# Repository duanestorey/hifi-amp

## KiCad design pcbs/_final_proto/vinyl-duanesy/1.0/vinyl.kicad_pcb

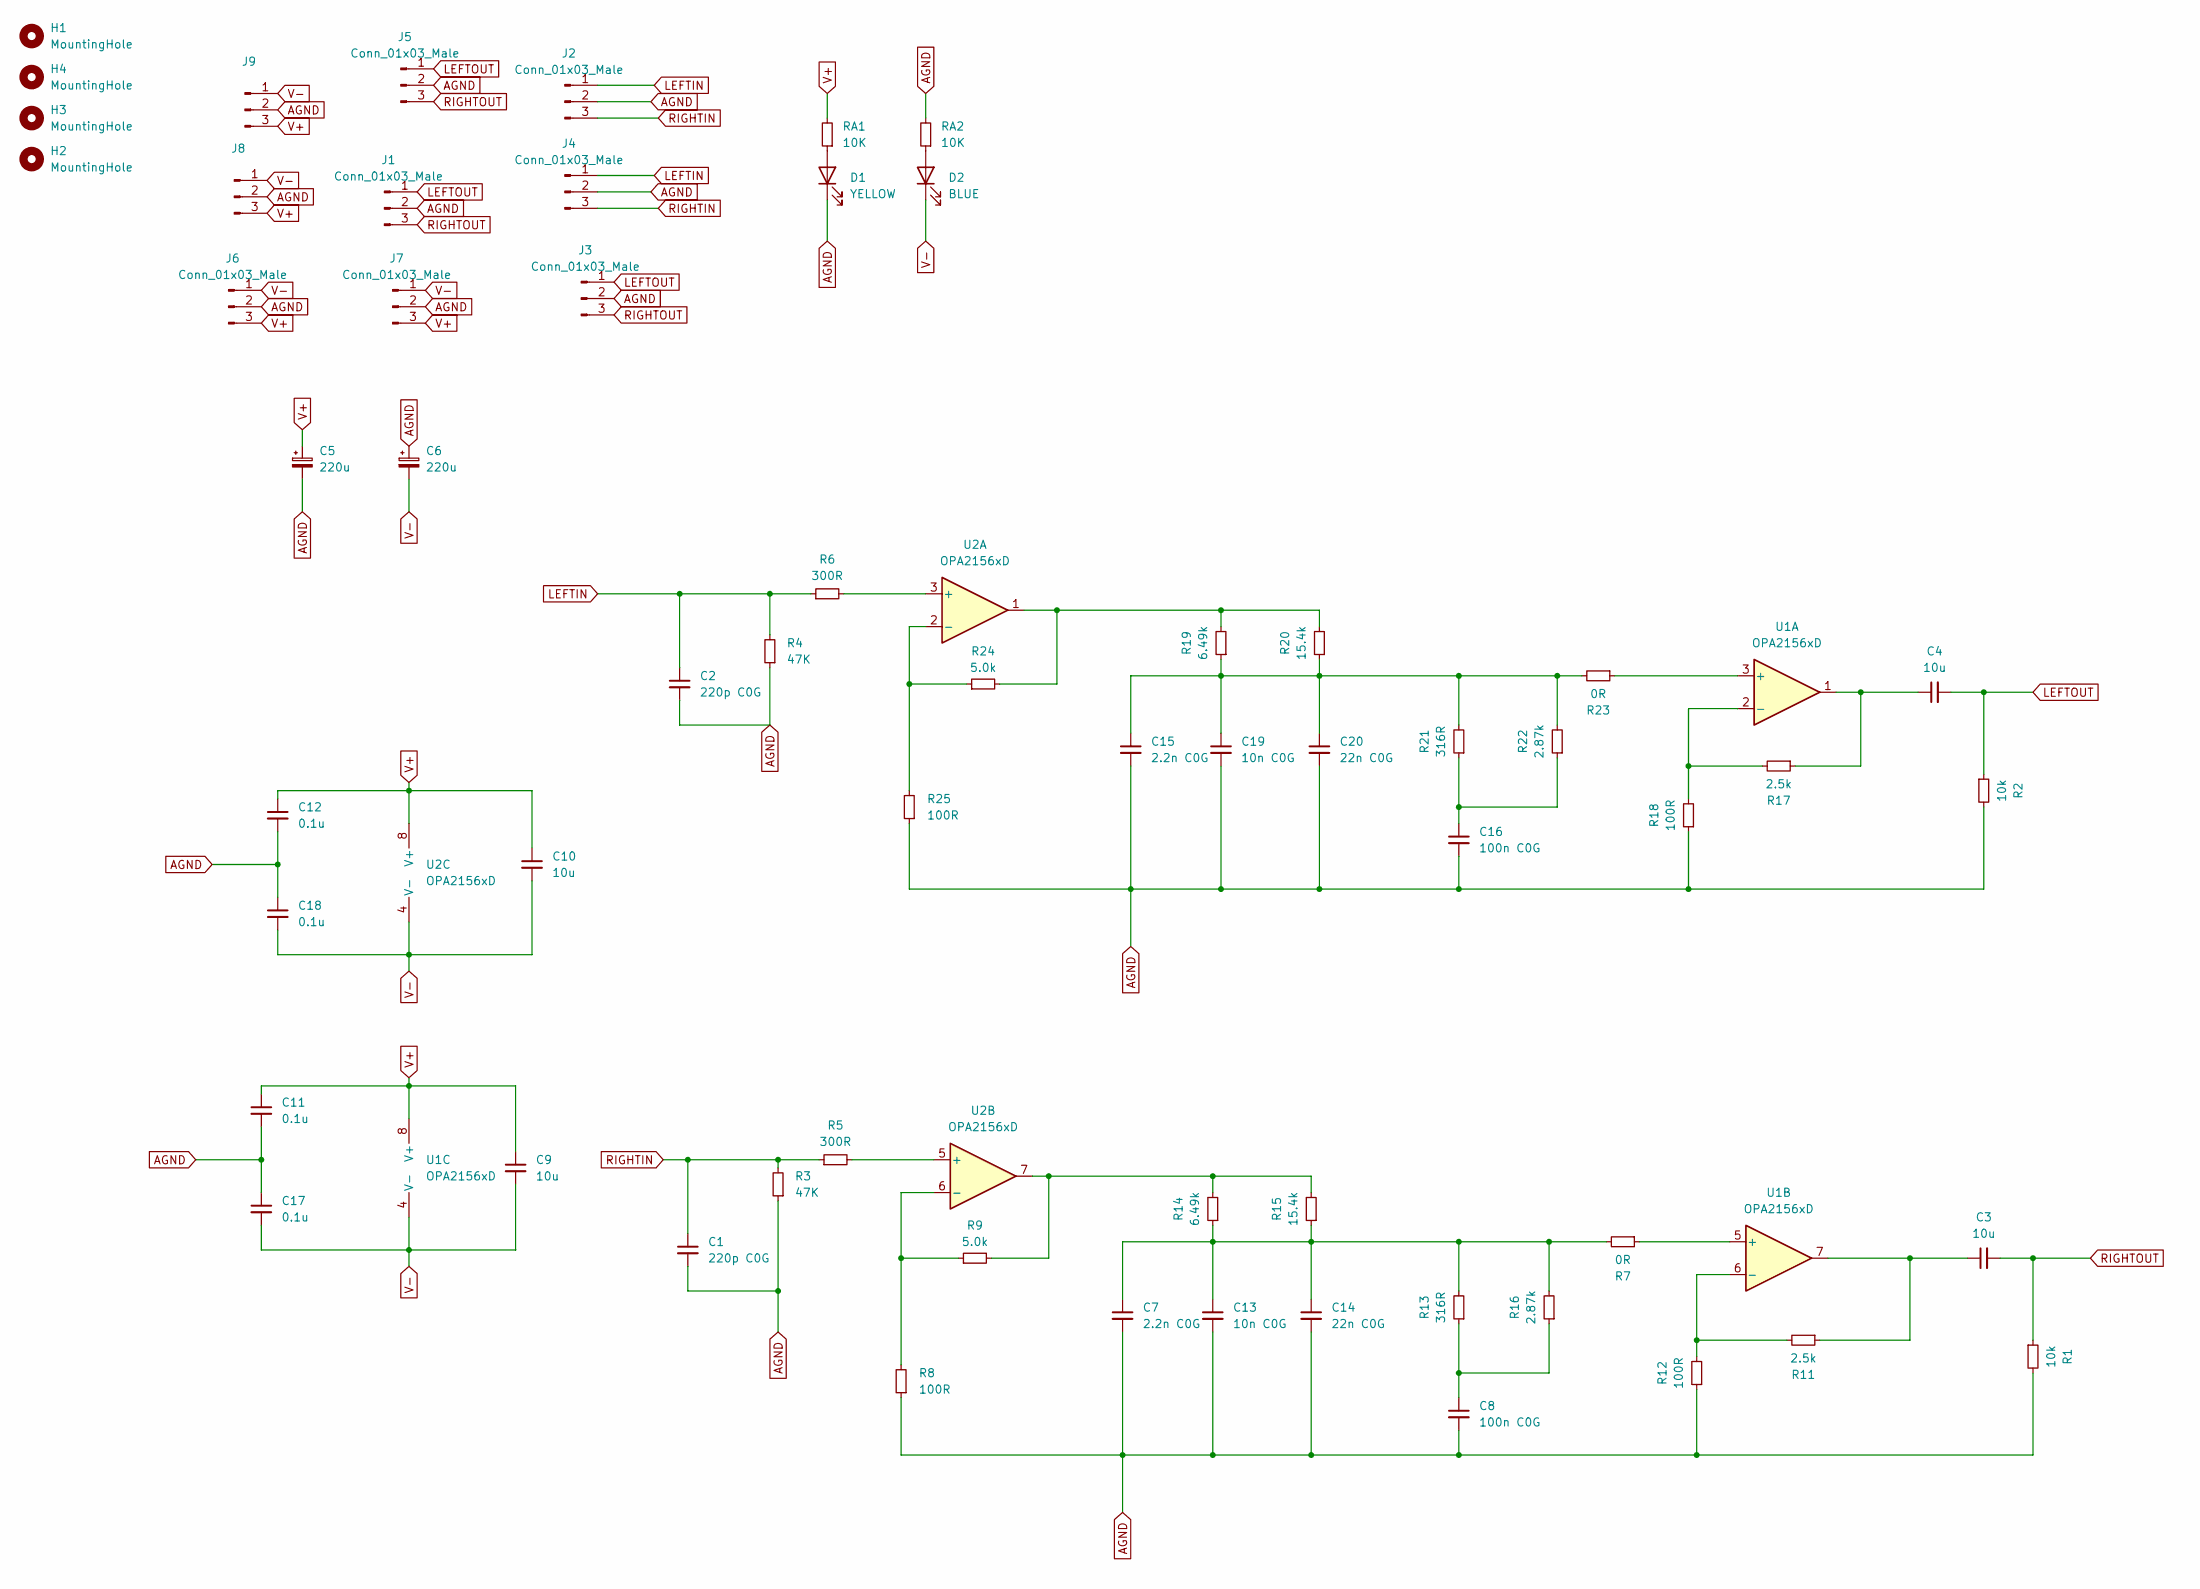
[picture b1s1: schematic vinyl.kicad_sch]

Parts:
C1, C2: 220p C0G; C_0805_2012Metric_Pad1.18x1.45mm_HandSolder_Duane; Mouser 791-0805N221F500CT
C3, C4: 10u; CP_Radial_D5.0mm_P2.00mm
C5, C6: 220u; CP_Elec_6.3x7.7
C7, C15: 2.2n C0G; C_0805_2012Metric_Pad1.18x1.45mm_HandSolder_Duane; Mouser 791-0805N222F500CT
C8, C16: 100n C0G; C_1206_3216Metric_Pad1.33x1.80mm_HandSolder_Duane; Mouser 81-GRT31C5C1H104FA2L
C9, C10: 10u; C_1206_3216Metric_Pad1.33x1.80mm_HandSolder_Duane
C11, C12, C17, C18: 0.1u; C_0805_2012Metric_Pad1.18x1.45mm_HandSolder_Duane
C13, C19: 10n C0G; C_0805_2012Metric_Pad1.18x1.45mm_HandSolder_Duane; Mouser 791-0805N103F500CT
C14, C20: 22n C0G; C_0805_2012Metric_Pad1.18x1.45mm_HandSolder_Duane; Mouser 81-GCM21B5C1H223FA6L
D1: YELLOW; LED_0805_2012Metric_Pad_HandSolder_Duane
D2: BLUE; LED_0805_2012Metric_Pad_HandSolder_Duane
H1, H2, H3, H4: MountingHole; MountingHole_3.2mm_M3_DIN965_Pad_TopOnly
J1, J2, J8, J9: Conn_01x03_Male; JST_PH_B3B-PH-K_1x03_P2.00mm_Vertical
J3, J4, J6, J7: Conn_01x03_Male; TerminalBlock_Phoenix_PT-1,5-3-5.0-H_1x03_P5.00mm_Horizontal
J5: Conn_01x03_Male; PinHeader_1x03_P2.54mm_Vertical
R1, R2: 10k; R_0805_2012Metric_Pad1.20x1.40mm_HandSolder_Duane; Mouser 754-RG2012P-103-B-T5
R3, R4: 47K; R_0805_2012Metric_Pad1.20x1.40mm_HandSolder_Duane; Mouser 603-RT0805BRD0747KL
R5, R6: 300R; R_0805_2012Metric_Pad1.20x1.40mm_HandSolder_Duane; Mouser 603-RT0805BRD07300RL
R7, R23: 0R; R_0805_2012Metric_Pad1.20x1.40mm_HandSolder_Duane; Mouser 594-MCU0805MZ0000ZP5
R8, R12, R18, R25: 100R; R_0805_2012Metric_Pad1.20x1.40mm_HandSolder_Duane; Mouser 708-RNCF0805BTE100R
R9, R24: 5.0k; R_0805_2012Metric_Pad1.20x1.40mm_HandSolder_Duane; Mouser 652-CRT0805BY5001EAS
R11, R17: 2.5k; R_0805_2012Metric_Pad1.20x1.40mm_HandSolder_Duane; Mouser PTN0805E2501BST1
R13, R21: 316R; R_0805_2012Metric_Pad1.20x1.40mm_HandSolder_Duane; Mouser 71-TNPW0805316RBEEA
R14, R19: 6.49k; R_0805_2012Metric_Pad1.20x1.40mm_HandSolder_Duane; Mouser RT0805BRD076K49L
R15, R20: 15.4k; R_0805_2012Metric_Pad1.20x1.40mm_HandSolder_Duane; Mouser RNCS0805BTE15K4
R16, R22: 2.87k; R_0805_2012Metric_Pad1.20x1.40mm_HandSolder_Duane; Mouser 667-ERA-6AEB2871V
RA1, RA2: 10K; R_0805_2012Metric_Pad1.20x1.40mm_HandSolder_Duane
U1, U2: OPA2156xD; DIP-8_W7.62mm_Socket

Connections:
AGND: C1.2, C2.2, C5.2, C6.1, C7.2, C8.2, C11.2, C12.2, C13.2, C14.2, C15.2, C16.2, C17.1, C18.1, C19.2, C20.2, D1.1 (K), J1.2, J2.2, J3.2, J4.2, J5.2, J6.2, J7.2, J8.2, J9.2, R1.2, R2.2, R3.1, R4.1, R8.1, R12.1, R18.1, R25.1, RA2.2
LEFTIN: C2.1, J2.1, J4.1, R4.2, R6.1
LEFTOUT: C4.2, J1.1, J3.1, J5.1, R2.1
unnamed: C3.1, R11.1, U1.7
unnamed: C4.1, R17.1, U1.1
unnamed: C8.1, R13.1, R16.1
unnamed: C7.1, C13.1, C14.1, R7.2, R13.2, R14.1, R15.1, R16.2
unnamed: C15.1, C19.1, C20.1, R19.1, R20.1, R21.2, R22.2, R23.2
unnamed: C16.1, R21.1, R22.1
unnamed: D1.2 (A), RA1.1
unnamed: D2.2 (A), RA2.1
unnamed: R9.2, R14.2, R15.2, U2.7
unnamed: R19.2, R20.2, R24.2, U2.1
unnamed: R23.1, U1.3 (+)
unnamed: R17.2, R18.2, U1.2 (-)
unnamed: R7.1, U1.5 (+)
unnamed: R11.2, R12.2, U1.6 (-)
unnamed: R6.2, U2.3 (+)
unnamed: R24.1, R25.2, U2.2 (-)
unnamed: R5.2, U2.5 (+)
unnamed: R8.2, R9.1, U2.6 (-)
RIGHTIN: C1.1, J2.3, J4.3, R3.2, R5.1
RIGHTOUT: C3.2, J1.3, J3.3, J5.3, R1.1
V+: C5.1, C9.1, C10.1, C11.1, C12.1, J6.3, J7.3, J8.3, J9.3, RA1.2, U1.8 (V+), U2.8 (V+)
V-: C6.2, C9.2, C10.2, C17.2, C18.2, D2.1 (K), J6.1, J7.1, J8.1, J9.1, U1.4 (V-), U2.4 (V-)

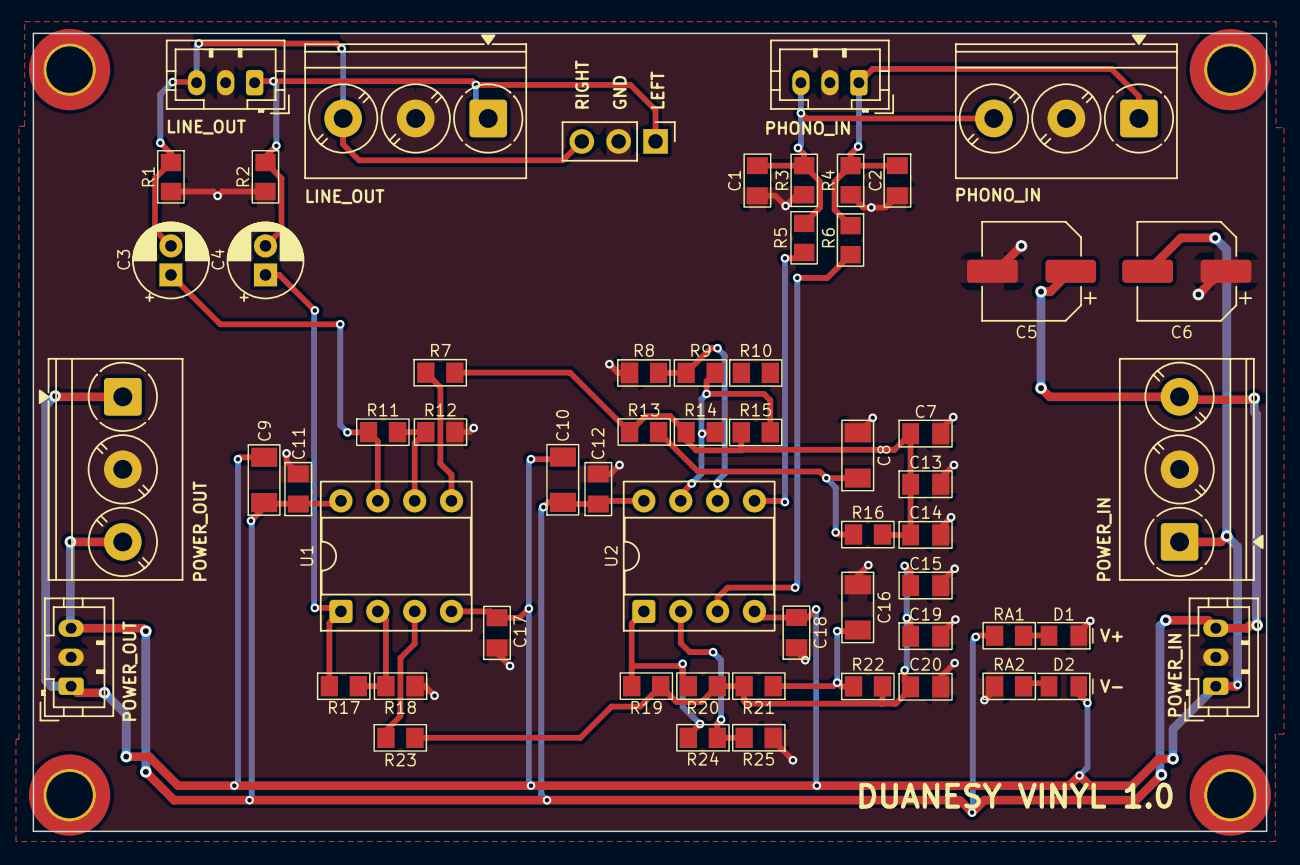
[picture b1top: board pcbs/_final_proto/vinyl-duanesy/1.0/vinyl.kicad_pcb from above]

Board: 2 copper layers, 85.0 x 55.0 mm, 64 parts (0 on the bottom side), 25 nets.

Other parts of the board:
R10: Unconnected; R_0805_2012Metric_Pad1.20x1.40mm_HandSolder_Duane

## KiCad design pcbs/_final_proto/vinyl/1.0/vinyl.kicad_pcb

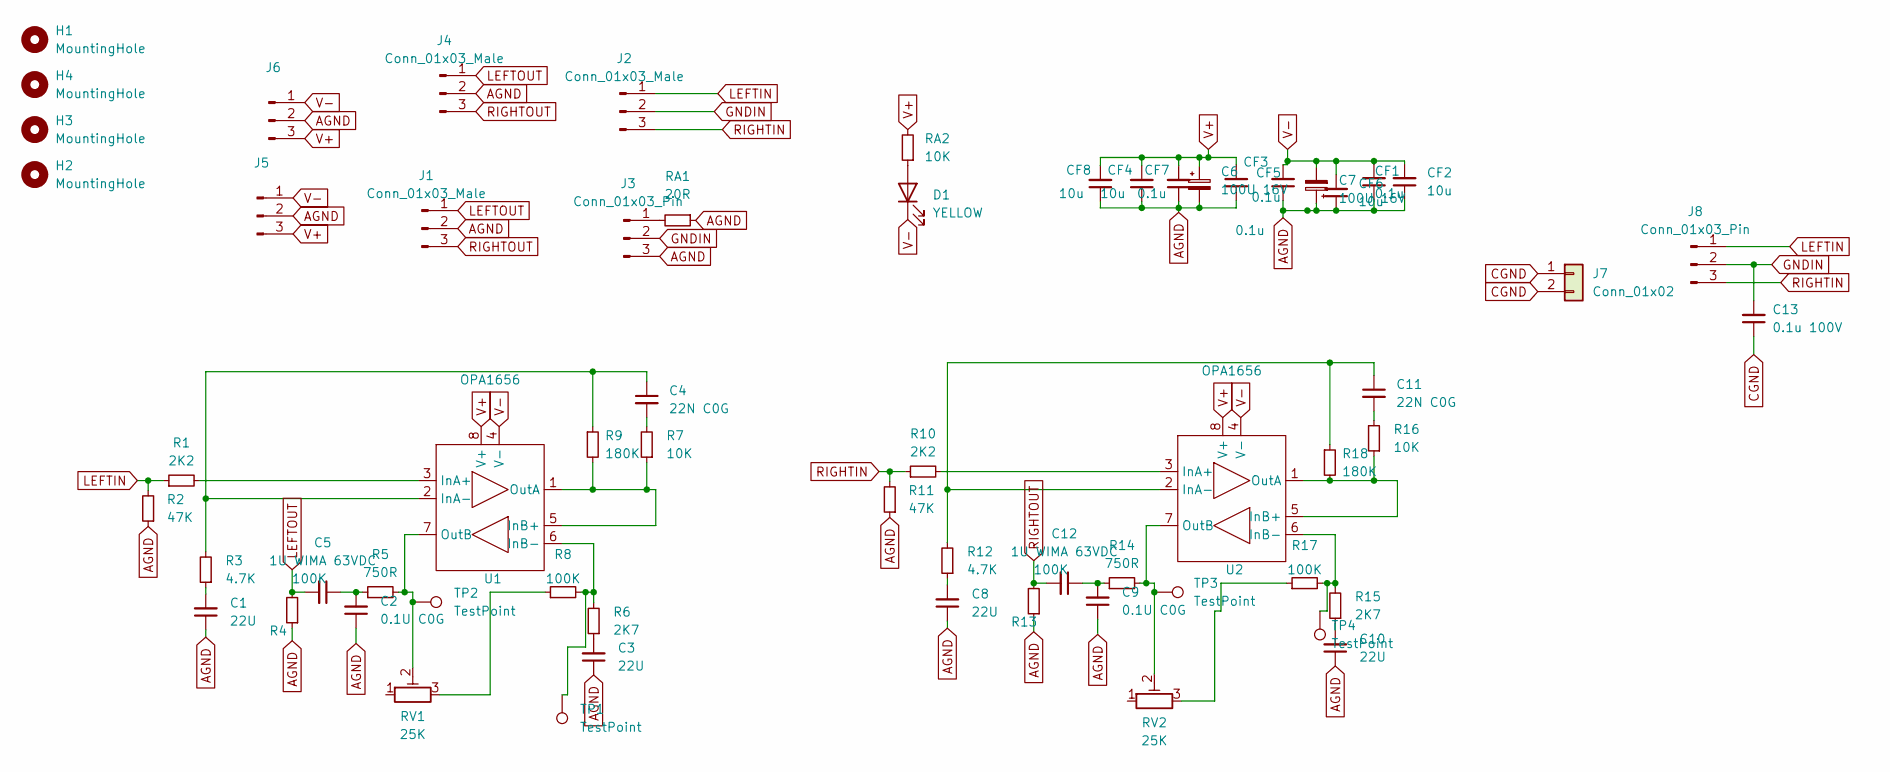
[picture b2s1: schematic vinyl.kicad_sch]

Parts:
C1, C3, C8, C10: 22U; CP_Radial_D6.3mm_P2.50mm
C2, C9: 0.1U C0G; C_1206_3216Metric_Pad1.33x1.80mm_HandSolder; Mouser 81-GRM3195C1H104GA5D
C4, C11: 22N C0G; C_0805_2012Metric_Pad1.18x1.45mm_HandSolder
C5, C12: 1U WIMA 63VDC; C_Rect_L7.2mm_W11.0mm_P5.00mm_FKS2_FKP2_MKS2_MKP2; Mouser 505-MKP2C0411NMN
C6, C7: 100U 16V; CP_Radial_D6.3mm_P2.50mm
C13: 0.1u 100V; C_1206_3216Metric; Mouser 791-1206B104K101CT
CF1, CF3, CF5, CF7: 0.1u; C_0805_2012Metric_Pad1.18x1.45mm_HandSolder
CF2, CF4, CF6, CF8: 10u; C_1206_3216Metric_Pad1.33x1.80mm_HandSolder
D1: YELLOW; LED_0805_2012Metric_Pad1.15x1.40mm_HandSolder
H1, H2, H3, H4: MountingHole; MountingHole_3.2mm_M3_DIN965_Pad_TopOnly
J1, J2, J5, J6: Conn_01x03_Male; JST_PH_B3B-PH-K_1x03_P2.00mm_Vertical
J3: Conn_01x03_Pin; PinHeader_1x03_P2.54mm_Vertical
J4: Conn_01x03_Male; PinHeader_1x03_P2.54mm_Vertical
J7: Conn_01x02; TerminalBlock_Phoenix_PT-1,5-2-3.5-H_1x02_P3.50mm_Horizontal
J8: Conn_01x03_Pin; TerminalBlock_Phoenix_PT-1,5-3-3.5-H_1x03_P3.50mm_Horizontal
R1, R10: 2K2; R_0805_2012Metric_Pad1.20x1.40mm_HandSolder; Mouser 603-RT0805FRE072K2L
R2, R11: 47K; R_0805_2012Metric_Pad1.20x1.40mm_HandSolder; Mouser 603-RT0805FRE0747KL
R3, R12: 4.7K; R_0805_2012Metric_Pad1.20x1.40mm_HandSolder; Mouser 603-RT0805FRE074K7L
R4, R8, R13, R17: 100K; R_0805_2012Metric_Pad1.20x1.40mm_HandSolder; Mouser 603-RT0805FRE10100KL
R5, R14: 750R; R_0805_2012Metric_Pad1.20x1.40mm_HandSolder; Mouser 603-RT0805FRE07750RL
R6, R15: 2K7; R_0805_2012Metric_Pad1.20x1.40mm_HandSolder; Mouser 603-RT0805FRE072K7L
R7, R16: 10K; R_0805_2012Metric_Pad1.20x1.40mm_HandSolder; Mouser 603-RT0805FRE1310KL
R9, R18: 180K; R_0805_2012Metric_Pad1.20x1.40mm_HandSolder; Mouser 603-RT0805FRE07180KL
RA1: 20R; R_0805_2012Metric_Pad1.20x1.40mm_HandSolder
RA2: 10K; R_0805_2012Metric_Pad1.20x1.40mm_HandSolder
RV1, RV2: 25K; Potentiometer_Bourns_3296W_Vertical
TP1, TP2, TP3, TP4: TestPoint; TestPoint_THTPad_1.5x1.5mm_Drill0.7mm
U1, U2: OPA1656; DIP-8_W7.62mm_Socket; Mouser 595-OPA1656IDR

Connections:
AGND: C1.1, C2.1, C3.1, C6.2, C7.1, C8.1, C9.1, C10.1, CF1.1, CF2.1, CF3.1, CF4.1, CF5.1, CF6.1, CF7.1, CF8.1, J1.2, J3.3, J4.2, J5.2, J6.2, R2.1, R4.1, R11.1, R13.1, RA1.1
CGND: C13.1, J7.1, J7.2
GNDIN: C13.2, J2.2, J3.2, J8.2
LEFTIN: J2.1, J8.1, R1.1, R2.2
LEFTOUT: C5.2, J1.1, J4.1, R4.2
unnamed: C1.2, R3.1
unnamed: C2.2, C5.1, R5.1
unnamed: C3.2, R6.1
unnamed: C4.2, R7.2
unnamed: C8.2, R12.1
unnamed: C10.2, R15.1
unnamed: C11.2, R16.2
unnamed: C9.2, C12.1, R14.1
unnamed: D1.2 (A), RA2.1
unnamed: J3.1, RA1.2
unnamed: R8.1, RV1.3
unnamed: R17.1, RV2.3
unnamed: R1.2, U1.3 (InA+)
unnamed: C4.1, R3.2, R9.1, U1.2 (InA-)
unnamed: R7.1, R9.2, U1.1 (OutA), U1.5 (InB+)
unnamed: R6.2, R8.2, TP1.1, U1.6 (InB-)
unnamed: R5.2, RV1.2, TP2.1, U1.7 (OutB)
unnamed: R10.2, U2.3 (InA+)
unnamed: C11.1, R12.2, R18.1, U2.2 (InA-)
unnamed: R16.1, R18.2, U2.1 (OutA), U2.5 (InB+)
unnamed: R15.2, R17.2, TP4.1, U2.6 (InB-)
unnamed: R14.2, RV2.2, TP3.1, U2.7 (OutB)
RIGHTIN: J2.3, J8.3, R10.1, R11.2
RIGHTOUT: C12.2, J1.3, J4.3, R13.2
V+: C6.1, CF3.2, CF4.2, CF7.2, CF8.2, J5.3, J6.3, RA2.2, U1.8 (V+), U2.8 (V+)
V-: C7.2, CF1.2, CF2.2, CF5.2, CF6.2, D1.1 (K), J5.1, J6.1, U1.4 (V-), U2.4 (V-)

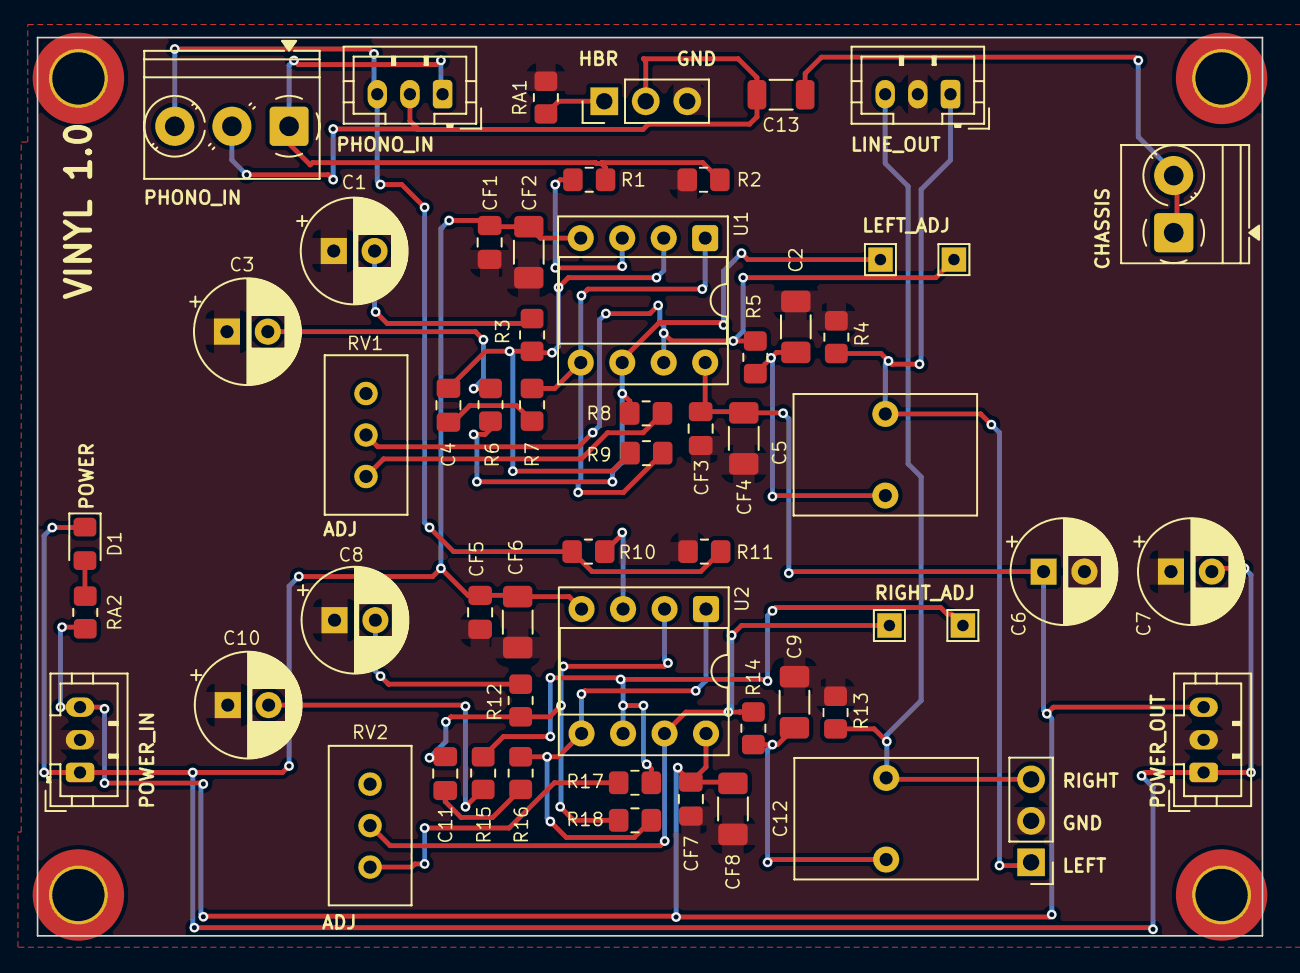
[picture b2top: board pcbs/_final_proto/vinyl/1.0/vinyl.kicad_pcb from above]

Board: 2 copper layers, 75.0 x 55.0 mm, 62 parts (0 on the bottom side), 31 nets.

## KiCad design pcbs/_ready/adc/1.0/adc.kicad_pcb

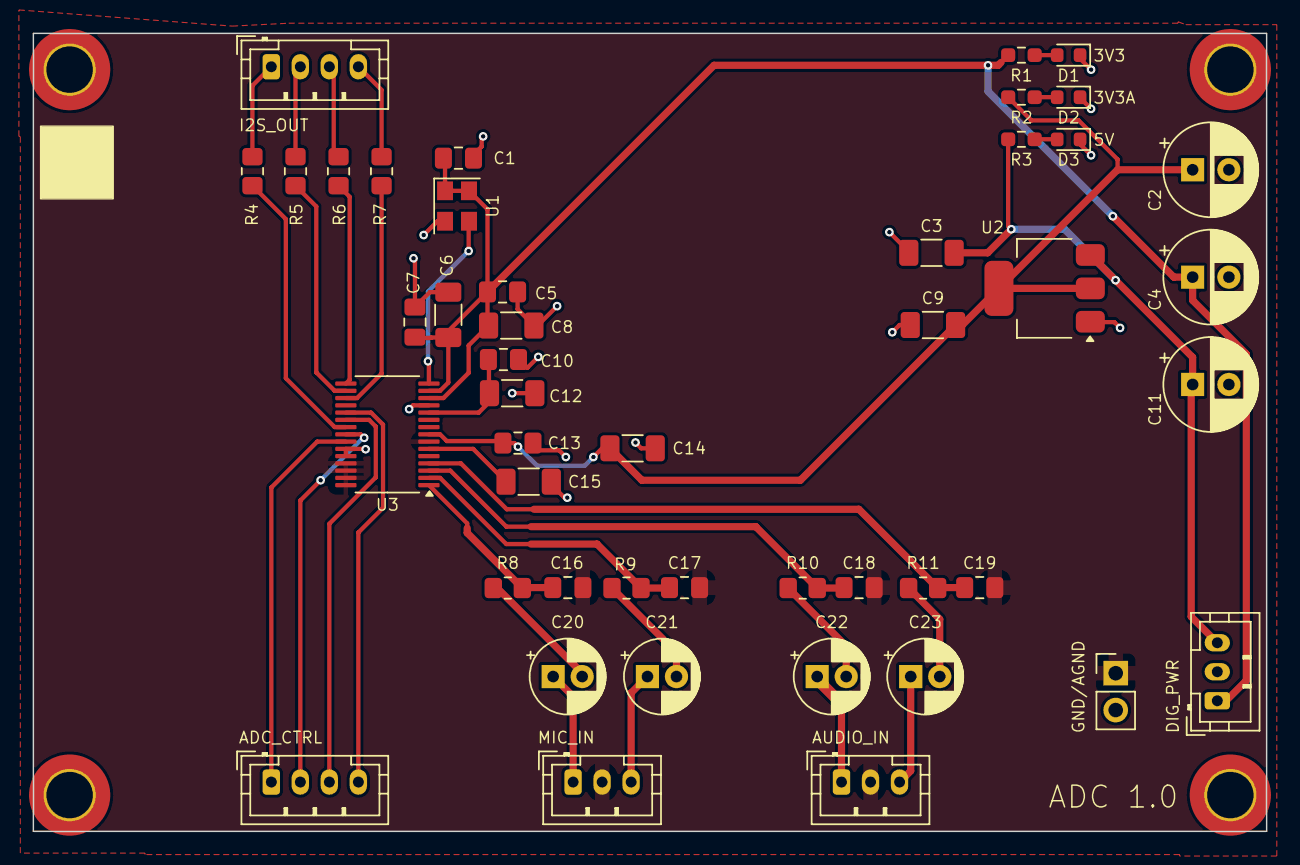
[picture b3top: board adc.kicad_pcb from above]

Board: 2 copper layers, 85.0 x 55.0 mm, 50 parts (0 on the bottom side), 35 nets.

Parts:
C1, C5, C7, C10, C13: 0.1u; C_0805_2012Metric_Pad1.18x1.45mm_HandSolder
C2, C4, C11: 470u; CP_Radial_D6.3mm_P2.50mm
C3, C6, C8, C9, C12, C14: 10u; C_1206_3216Metric_Pad1.33x1.80mm_HandSolder
C15: 1u; C_1206_3216Metric_Pad1.33x1.80mm_HandSolder
C16, C17, C18, C19: 10n C0G; C_0805_2012Metric_Pad1.18x1.45mm_HandSolder
C20, C21, C22, C23: 10u NICHICON 25V; CP_Radial_D5.0mm_P2.00mm
D1, D3: BLUE; LED_0603_1608Metric
D2: YELLOW; LED_0603_1608Metric
H1, H2, H3, H4: MountingHole; MountingHole_3.2mm_M3_DIN965_Pad_TopOnly
J1, J4: Conn_01x04_Pin; JST_PH_B4B-PH-K_1x04_P2.00mm_Vertical
J2: Conn_01x02_Male; PinHeader_1x02_P2.54mm_Vertical
J3, J5, J6: Conn_01x03_Pin; JST_PH_B3B-PH-K_1x03_P2.00mm_Vertical
R1: 150R; R_0603_1608Metric_Pad0.98x0.95mm_HandSolder
R2: 650R; R_0603_1608Metric_Pad0.98x0.95mm_HandSolder
R3: 1.3K; R_0603_1608Metric_Pad0.98x0.95mm_HandSolder
R4, R5, R6, R7: 22R; R_0805_2012Metric_Pad1.20x1.40mm_HandSolder
R8, R9, R10, R11: 100R; R_0805_2012Metric_Pad1.20x1.40mm_HandSolder
U1: ASDMB-xxxMHz; Oscillator_SMD_Abracon_ASE-4Pin_3.2x2.5mm
U2: ZLDO1117QG33TA; SOT-223-3_TabPin2
U3: PCM1863; TSSOP-30_4.4x7.8mm_P0.5mm

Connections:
3V3: C1.1, C4.1, C5.1, C6.1, C7.1, C8.1, J3.1, R1.2, U1.1 (Standby), U1.4 (VDD), U3.13 (DVDD), U3.14 (IOVDD)
3V3A: C2.1, C9.2, C13.1, C14.1, R2.2, U2.2 (VO), U3.8 (AVDD)
5V: C3.2, C11.1, J3.3, R3.2, U2.3 (VI)
ADC_GPIO1: J4.3, U3.21 (GPIO1/INTA/DMI)
ADC_INT: J4.4, U3.20 (GPIO2/INTB/DMCLK)
AGND: C16.1, C17.2, C18.1, C19.2, J2.1, J5.2, J6.2, U3.7 (AGND), U3.27 (VINL4), U3.28 (VINR4), U3.29 (VINL3), U3.30 (VINR3)
GND: C1.2, C3.1, C4.2, C5.2, C6.2, C7.2, C8.2, C9.1, C10.2, C11.2, C12.2, C13.2, C14.2, C15.2, D1.1 (K), D2.1 (K), D3.1 (K), J2.2, J3.2, U1.2 (GND), U2.1 (GND), U3.12 (DGND), U3.25 (MS/AD), U3.26 (MD0)
I2S_BCLK_OUT: J1.2, R5.2
I2S_DATA_OUT: J1.4, R7.2
I2S_LRCLK_OUT: J1.3, R6.2
I2S_MCLK_OUT: J1.1, R4.2
LDO: C10.1, C12.1, U3.11 (LDO)
LEFT_IN: C22.1, J6.1
MIC_LEFT_IN: C20.1, J5.1
MIC_RIGHT_IN: C21.1, J5.3
unnamed: C20.2, R8.1
unnamed: C21.2, R9.1
unnamed: C22.2, R10.1
unnamed: C23.2, R11.1
unnamed: D1.2 (A), R1.1
unnamed: D2.2 (A), R2.1
unnamed: D3.2 (A), R3.1
unnamed: R5.1, U3.17 (BCLK)
unnamed: R7.1, U3.18 (DOUT)
unnamed: R6.1, U3.16 (LRCLK)
unnamed: R4.1, U3.22 (MOSI/GPIO0/DMIN2)
unnamed: C18.2, R10.2, U3.3 (VINL1)
unnamed: C16.2, R8.2, U3.1 (VINL2)
unnamed: C19.1, R11.2, U3.4 (VINR1)
unnamed: C17.1, R9.2, U3.2 (VINR2)
RIGHT_IN: C23.1, J6.3
SCL: J4.1, U3.24 (MC/SCL)
SCLKI: U1.3 (Out), U3.15 (SCLKI)
SDA: J4.2, U3.23 (MOSI/SDA)
VREF: C15.1, U3.6 (VREF)

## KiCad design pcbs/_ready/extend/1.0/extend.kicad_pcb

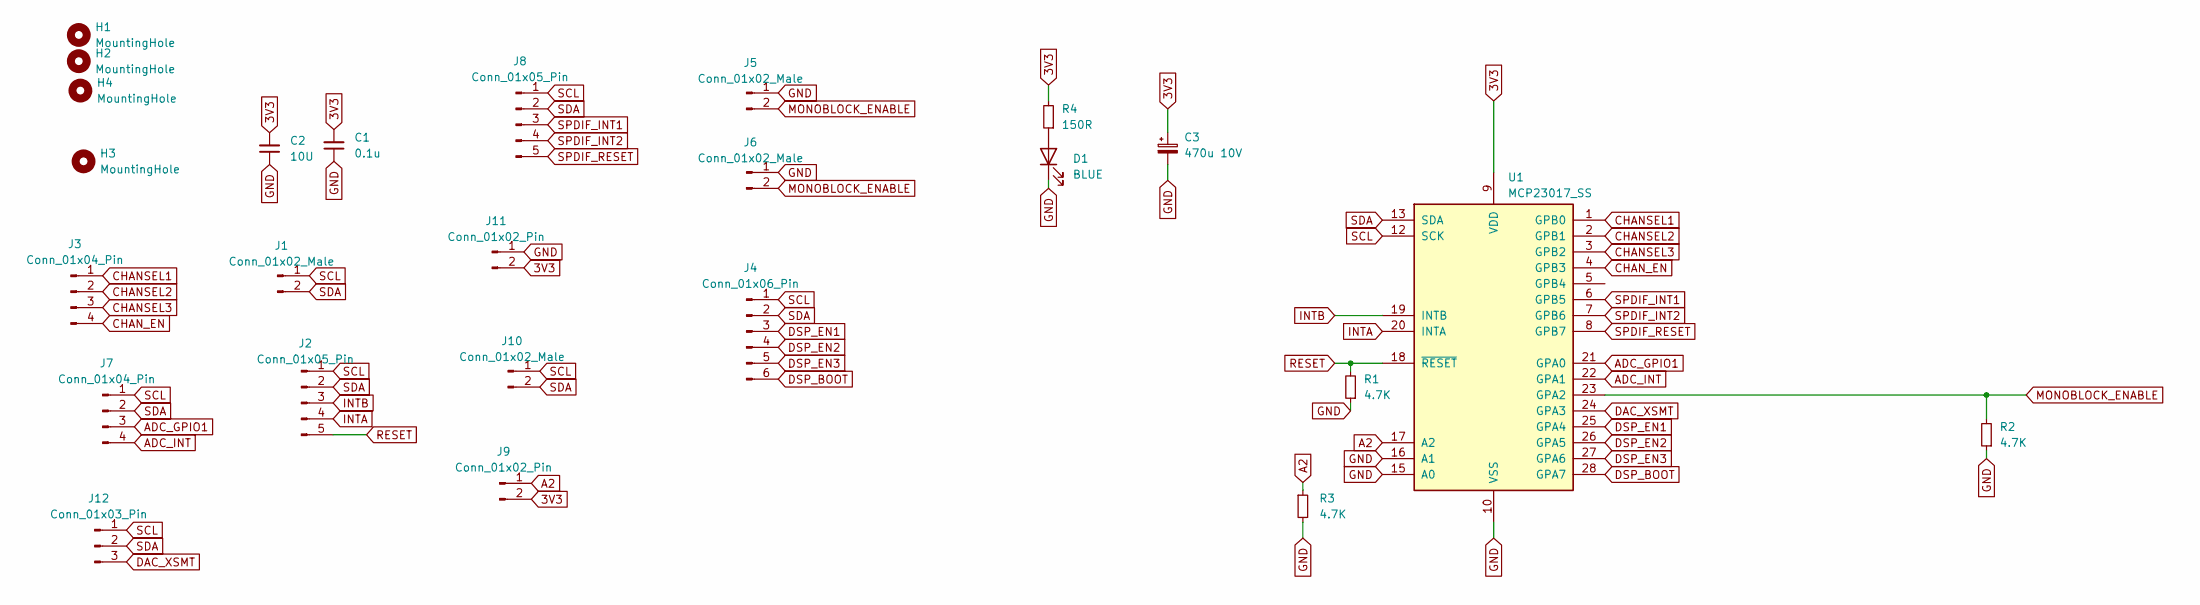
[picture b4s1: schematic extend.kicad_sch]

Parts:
C1: 0.1u; C_0805_2012Metric_Pad1.18x1.45mm_HandSolder
C2: 10U; C_1206_3216Metric_Pad1.33x1.80mm_HandSolder
C3: 470u 10V; CP_Radial_D6.3mm_P2.50mm
D1: BLUE; LED_0603_1608Metric
H1, H2, H3, H4: MountingHole; MountingHole_3.2mm_M3_DIN965_Pad_TopOnly
J1, J5, J6, J10: Conn_01x02_Male; JST_PH_B2B-PH-K_1x02_P2.00mm_Vertical
J2, J8: Conn_01x05_Pin; JST_PH_B5B-PH-K_1x05_P2.00mm_Vertical
J3, J7: Conn_01x04_Pin; JST_PH_B4B-PH-K_1x04_P2.00mm_Vertical
J4: Conn_01x06_Pin; JST_PH_B6B-PH-K_1x06_P2.00mm_Vertical
J9: Conn_01x02_Pin; PinHeader_1x02_P2.54mm_Vertical
J11: Conn_01x02_Pin; JST_PH_B2B-PH-K_1x02_P2.00mm_Vertical
J12: Conn_01x03_Pin; JST_PH_B3B-PH-K_1x03_P2.00mm_Vertical
R1, R2, R3: 4.7K; R_0603_1608Metric_Pad0.98x0.95mm_HandSolder
R4: 150R; R_0603_1608Metric
U1: MCP23017_SS; SSOP-28_5.3x10.2mm_P0.65mm; Mouser 579-MCP23017-E/SS

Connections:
3V3: C1.2, C2.2, C3.1, J9.2, J11.2, R4.2, U1.9 (VDD)
A2: J9.1, R3.1, U1.17 (A2)
ADC_GPIO1: J7.3, U1.21 (GPA0)
ADC_INT: J7.4, U1.22 (GPA1)
CHANSEL1: J3.1, U1.1 (GPB0)
CHANSEL2: J3.2, U1.2 (GPB1)
CHANSEL3: J3.3, U1.3 (GPB2)
CHAN_EN: J3.4, U1.4 (GPB3)
DAC_XSMT: J12.3, U1.24 (GPA3)
DSP_BOOT: J4.6, U1.28 (GPA7)
DSP_EN1: J4.3, U1.25 (GPA4)
DSP_EN2: J4.4, U1.26 (GPA5)
DSP_EN3: J4.5, U1.27 (GPA6)
GND: C1.1, C2.1, C3.2, D1.1 (K), J5.1, J6.1, J11.1, R1.1, R2.1, R3.2, U1.10 (VSS), U1.15 (A0), U1.16 (A1)
INTA: J2.4, U1.20 (INTA)
INTB: J2.3, U1.19 (INTB)
MONOBLOCK_ENABLE: J5.2, J6.2, R2.2, U1.23 (GPA2)
unnamed: D1.2 (A), R4.1
RESET: J2.5, R1.2, U1.18 (~RESET)
SCL: J1.1, J2.1, J4.1, J7.1, J8.1, J10.1, J12.1, U1.12 (SCK)
SDA: J1.2, J2.2, J4.2, J7.2, J8.2, J10.2, J12.2, U1.13 (SDA)
SPDIF_INT1: J8.3, U1.6 (GPB5)
SPDIF_INT2: J8.4, U1.7 (GPB6)
SPDIF_RESET: J8.5, U1.8 (GPB7)

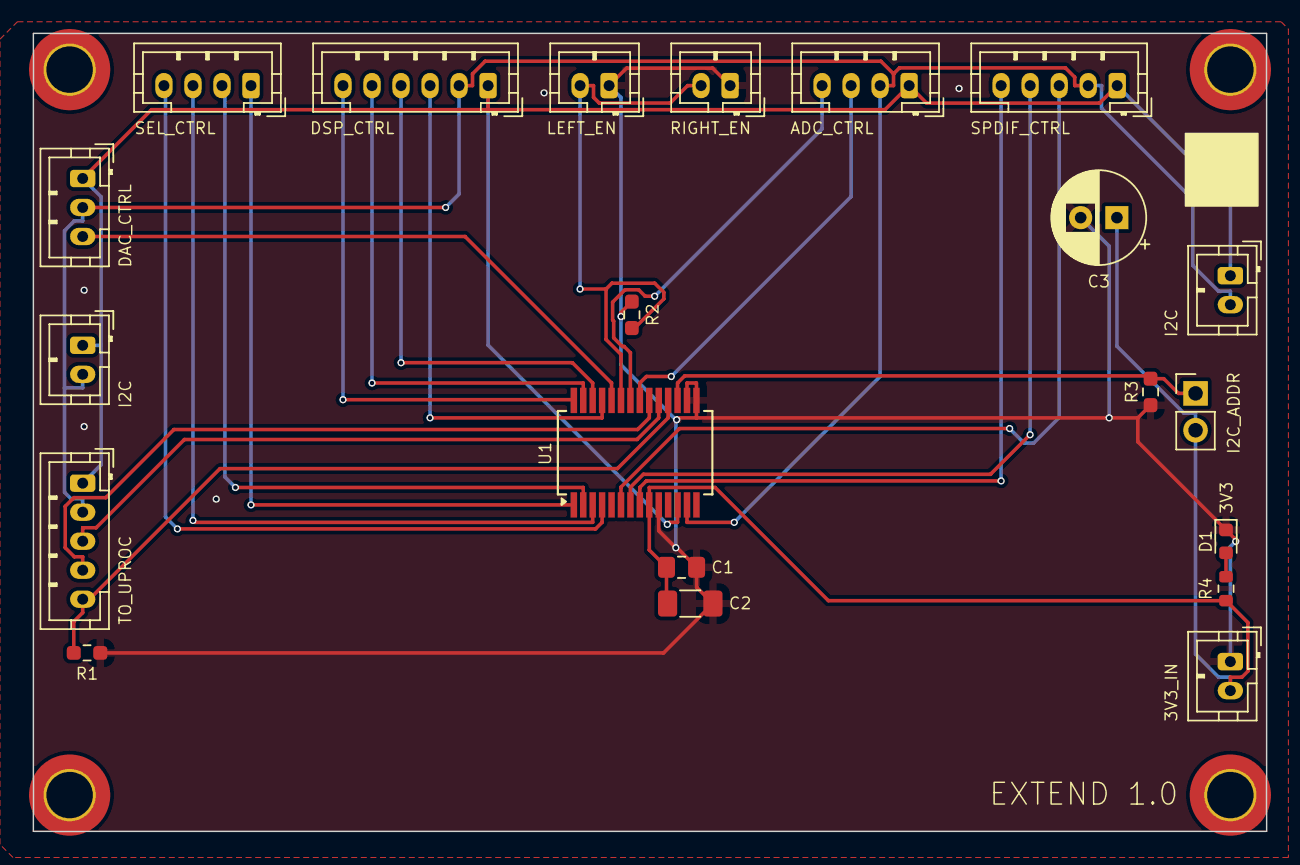
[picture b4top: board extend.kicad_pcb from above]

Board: 2 copper layers, 85.0 x 55.0 mm, 25 parts (0 on the bottom side), 24 nets.

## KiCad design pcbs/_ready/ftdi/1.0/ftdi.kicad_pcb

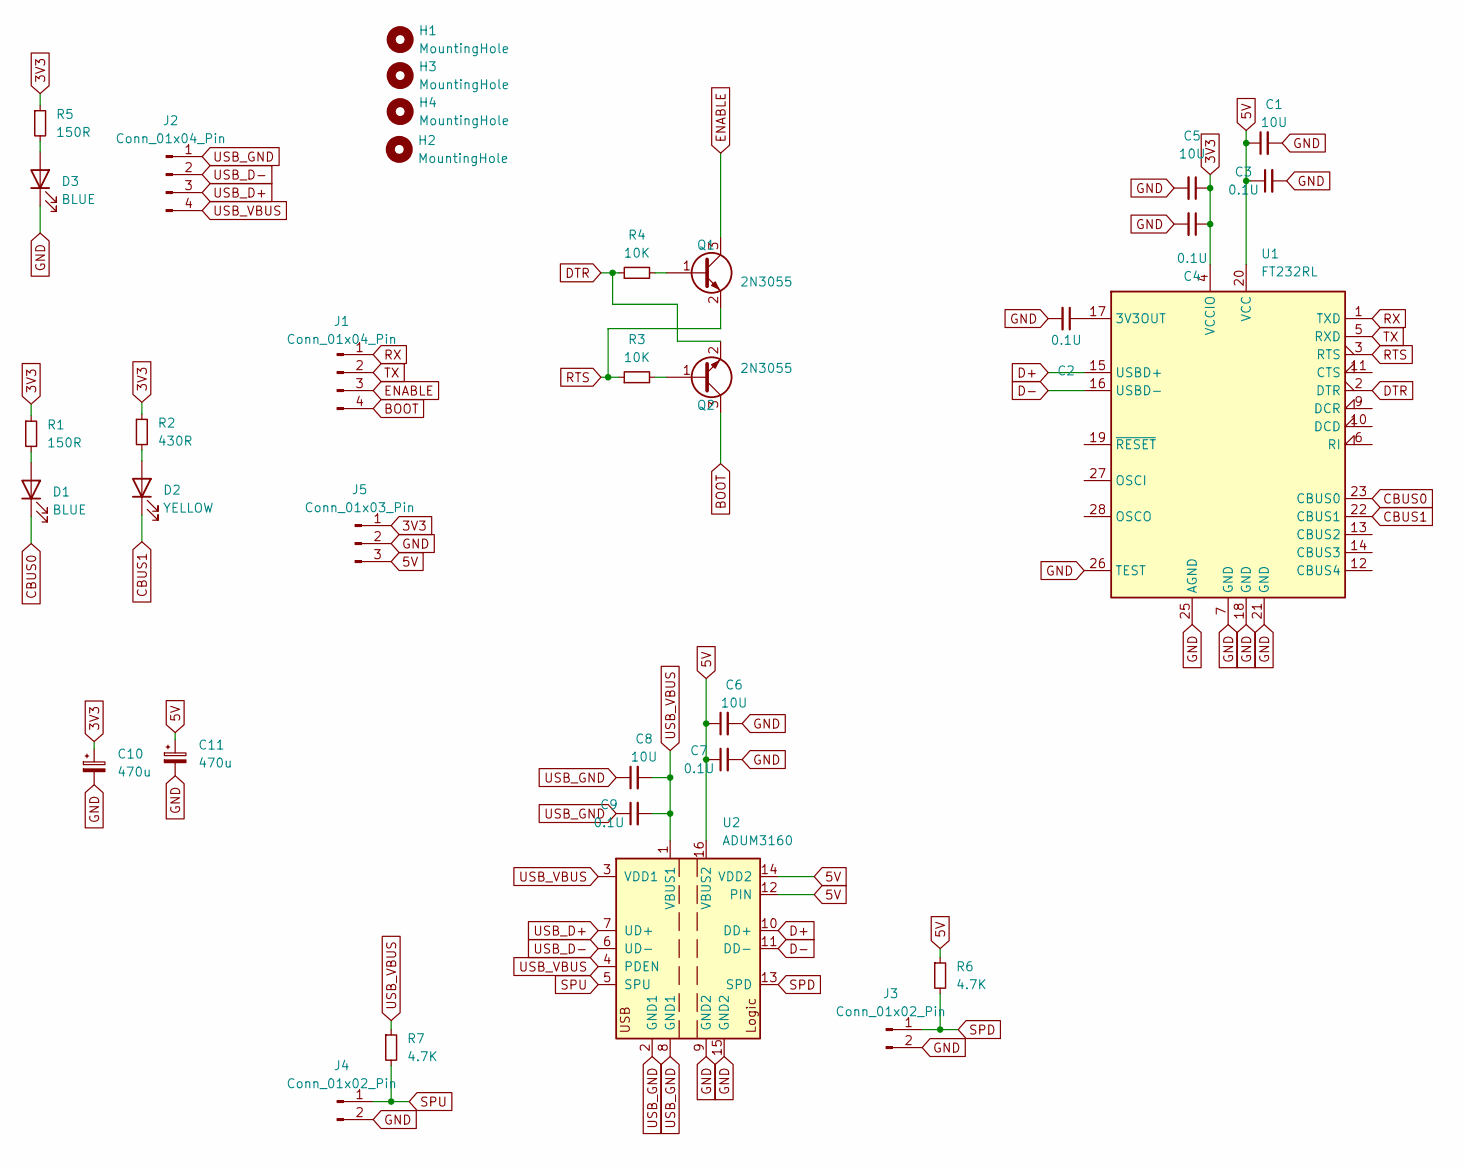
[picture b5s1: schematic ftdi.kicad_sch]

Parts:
C1, C5, C6, C8: 10U; C_1206_3216Metric_Pad1.33x1.80mm_HandSolder
C2, C3, C4, C7, C9: 0.1U; C_0805_2012Metric_Pad1.18x1.45mm_HandSolder
C10, C11: 470u; CP_Radial_D6.3mm_P2.50mm
D1, D3: BLUE; LED_0603_1608Metric_Pad1.05x0.95mm_HandSolder; LCSC XL-1608UBC-04
D2: YELLOW; LED_0603_1608Metric_Pad1.05x0.95mm_HandSolder; LCSC XL-1608UBC-04
H1, H2, H3, H4: MountingHole; MountingHole_3.2mm_M3_DIN965_Pad_TopOnly
J1, J2: Conn_01x04_Pin; JST_PH_B4B-PH-K_1x04_P2.00mm_Vertical
J3, J4: Conn_01x02_Pin; PinHeader_1x02_P2.54mm_Vertical
J5: Conn_01x03_Pin; JST_PH_B3B-PH-K_1x03_P2.00mm_Vertical
Q1, Q2: 2N3055; TSOT-23
R1, R5: 150R; R_0603_1608Metric_Pad0.98x0.95mm_HandSolder
R2: 430R; R_0603_1608Metric_Pad0.98x0.95mm_HandSolder
R3, R4: 10K; R_0603_1608Metric_Pad0.98x0.95mm_HandSolder
R6, R7: 4.7K; R_0603_1608Metric_Pad0.98x0.95mm_HandSolder
U1: FT232RL; SSOP-28_5.3x10.2mm_P0.65mm
U2: ADUM3160; SOIC-16W_7.5x10.3mm_P1.27mm; Mouser 584-ADUM3160BRWZ-R

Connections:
3V3: C4.1, C5.1, C10.1, J5.1, R1.1, R2.1, R5.1, U1.4 (VCCIO)
5V: C1.1, C3.1, C6.1, C7.1, C11.1, J5.3, R6.1, U1.20 (VCC), U2.12 (PIN), U2.14 (VDD2), U2.16 (VBUS2)
BOOT: J1.4, Q2.3 (C)
CBUS0: D1.1 (K), U1.23 (CBUS0)
CBUS1: D2.1 (K), U1.22 (CBUS1)
D+: U1.15 (USBD+), U2.10 (DD+)
D-: U1.16 (USBD-), U2.11 (DD-)
DTR: Q2.2 (E), R4.1, U1.2 (DTR)
ENABLE: J1.3, Q1.3 (C)
GND: C1.2, C2.2, C3.2, C4.2, C5.2, C6.2, C7.2, C10.2, C11.2, D3.1 (K), J3.2, J4.2, J5.2, U1.7 (GND), U1.18 (GND), U1.21 (GND), U1.25 (AGND), U1.26 (TEST), U2.9 (GND2), U2.15 (GND2)
unnamed: D1.2 (A), R1.2
unnamed: D2.2 (A), R2.2
unnamed: D3.2 (A), R5.2
unnamed: Q1.1 (B), R4.2
unnamed: Q2.1 (B), R3.2
unnamed: C2.1, U1.17 (3V3OUT)
RTS: Q1.2 (E), R3.1, U1.3 (RTS)
RX: J1.1, U1.1 (TXD)
SPD: J3.1, R6.2, U2.13 (SPD)
SPU: J4.1, R7.2, U2.5 (SPU)
TX: J1.2, U1.5 (RXD)
USB_D+: J2.3, U2.7 (UD+)
USB_D-: J2.2, U2.6 (UD-)
USB_GND: C8.1, C9.1, J2.1, U2.2 (GND1), U2.8 (GND1)
USB_VBUS: C8.2, C9.2, J2.4, R7.1, U2.1 (VBUS1), U2.3 (VDD1), U2.4 (PDEN)

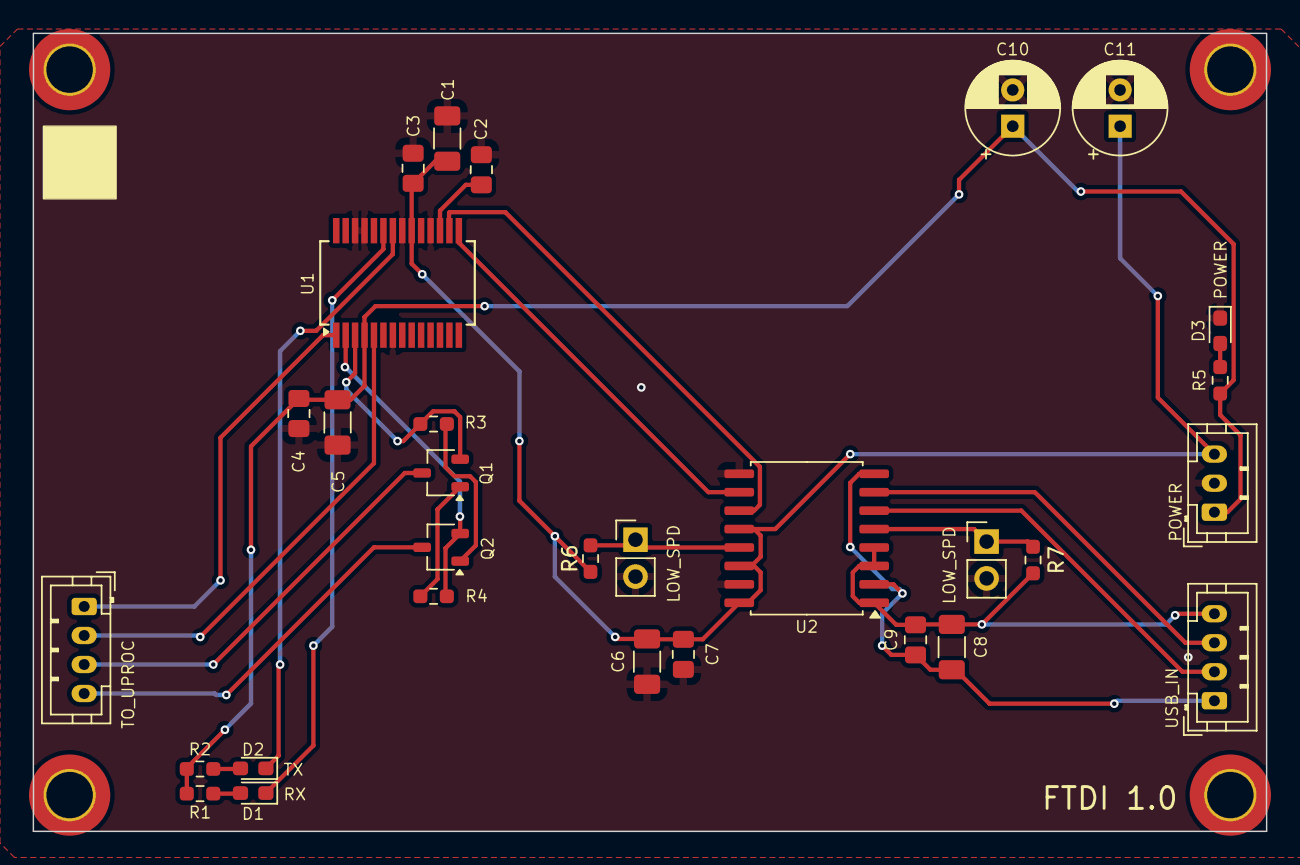
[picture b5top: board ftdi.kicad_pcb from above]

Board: 2 copper layers, 85.0 x 55.0 mm, 34 parts (0 on the bottom side), 25 nets.
